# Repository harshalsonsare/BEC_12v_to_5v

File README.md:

# KiCad Hardware Design & Automation Workspace

A complete, production-verified hardware repository featuring a high-efficiency **12V-to-5V 3A Synchronous Buck Converter (BEC)**, engineered and verified using **KiCad 10** and the **KiCad MCP (Model Context Protocol) Server** in Google Antigravity.

---

## 3D Hardware & PCB Showcase

<p align="center">
  &nbsp;
  
</p>
<p align="center">
  <em>Figure 1: 3D Raytraced Model (Top) | Top Layer High-Current Routing & SilkS (Left) | Bottom Layer Shielded FB Trace & Solid GND (Right)</em>
</p>

<p align="center">
  <em>Figure 2: Verified Schematic (TI TPS54302, Protection Diode, Passives & Connectors)</em>
</p>

---

## 1. Project Overview & Specifications

### 12V-to-5V 3A Battery Eliminator Circuit (BEC)
Designed for robotics, UAV/FPV drones, RC models, and embedded computing (e.g. powering Raspberry Pi, flight controllers, and high-torque 5V servos from a 3S–4S LiPo battery or 12V DC rail).

| Parameter | Specification | Notes / Rationale |
| :--- | :--- | :--- |
| **Input Voltage ($V_{IN}$)** | **12 V nominal** (4.5 V – 18.0 V operational) | Compatible with 3S (11.1 V–12.6 V) and 4S (14.8 V–16.8 V) LiPo packs |
| **Input Transient Protection** | **SM6T18A TVS Diode** (600 W, $V_{RM} = 15.3\text{ V}$, $V_C = 25.2\text{ V}$) | Clamps voltage spikes safely below IC 30 V absolute max |
| **Output Voltage ($V_{OUT}$)** | **5.00 V DC** | Set via precision 0.5% divider ($R_1 = 93.1\text{ k}\Omega$, $R_2 = 12.6\text{ k}\Omega$) |
| **Output Current ($I_{OUT}$)** | **3.0 A continuous** | Thermally sustained on 2-layer 1 oz copper board |
| **Switching Frequency ($f_{SW}$)** | **400 kHz** fixed frequency | Optimized balance between size and switching efficiency |
| **Regulator IC** | **TI TPS54302DDCR** (SOT-23-6) | Synchronous buck converter with integrated 85 mΩ / 40 mΩ MOSFETs |
| **Power Inductor** | **Bourns SRP7028A-100M** (10 µH, shielded) | $I_{sat} = 6.0\text{ A}$, $I_{rms} = 3.5\text{ A}$, DCR = 75 mΩ |
| **Input Decoupling** | $22\ \mu\text{F}$ 35V X5R (1210) + $100\text{ nF}$ 50V X7R (0805) | High-voltage 1210 prevents severe ceramic DC bias capacitance drop |
| **Output Decoupling** | $2\times 22\ \mu\text{F}$ 25V X7R (1206) | Low ESR (< 10 mΩ), voltage ripple < 20 mV pk-pk at 3A load |
| **Phase Margin Boost** | $75\text{ pF}$ C0G feedforward cap ($C_8$) across $R_1$ | Stabilizes loop phase margin (>60°) with ceramic output capacitors |
| **UVLO Protection** | Precision divider: $R_3 = 511\text{ k}\Omega$, $R_4 = 105\text{ k}\Omega$ | Starts at ~6.9 V, stops at ~5.7 V; protects EN pin (7 V abs max) |
| **Input Connector ($J_1$)** | **AMASS XT30PW-M** (Horizontal / Right-Angle PCB) | High-reliability DC connector rated up to 30 A |
| **Output Connector ($J_2$)** | **3-Pin 2.54 mm Vertical Pin Header** | Standard RC servo pinout (Pin 1: NC/Signal, Pin 2: +5V, Pin 3: GND) |
| **PCB Dimensions** | **25.0 mm × 18.0 mm** | Centered on standard A4 sheet ($X = 148.5\text{ mm}, Y = 105.0\text{ mm}$) |
| **Layer Stackup** | **2-Layer FR-4**, 1.6 mm thickness, 1 oz Cu | Dual solid ground planes with thermal stitching array |
| **Design Status** | **100% Routed & Verified** | **0 DRC violations, 0 unconnected items, 0 ERC errors** |

---

## 2. Repository Structure

```text
KiCad/
├── .agents/
│   └── rules/
│       └── kicad-pcb.md           # Persistent agent engineering rules (always_on)
├── docs/
│   ├── images/                    # Visual renderings & documentation figures
│   │   ├── pcb_3d_isometric.png   # 3D raytraced PCB model
│   │   ├── pcb_top.png            # Top layer routing & silkscreen
│   │   ├── pcb_bottom.png         # Bottom layer shielded FB & ground plane
│   │   └── schematic.png          # Capture schematic overview
│   └── lessons-learned.md         # Persistent engineering memory, quirks & solutions
├── bec_12v_to_5v/                 # Core 12V-to-5V BEC KiCad project
│   ├── bec_12v_to_5v.kicad_pro    # Project settings & net classes
│   ├── bec_12v_to_5v.kicad_sch    # Schematic capture
│   ├── bec_12v_to_5v.kicad_pcb    # 25x18mm 2-layer routed board
│   ├── bec_12v_to_5v.kicad_dru    # Design rules
│   └── exports/                   # Project-local mirror of manufacturing outputs
├── DemoPCB/                       # MCP server interactive testing & validation board
│   ├── DemoPCB.kicad_pro
│   ├── DemoPCB.kicad_sch
│   └── DemoPCB.kicad_pcb
├── exports/                       # Production manufacturing & assembly packages
│   ├── gerbers/                   # RS-274X copper, soldermask, paste, silkscreen, edge cuts
│   ├── drill/                     # Excellon PTH & NPTH drill files and drill report
│   ├── bom/                       # Full Bill of Materials (CSV)
│   ├── pos/                       # Pick-and-place centroid coordinates (CSV)
│   ├── 3d/                        # Standard 3D CAD model (STEP AP214/AP242)
│   └── svg/                       # High-resolution vector renderings (top & bottom)
├── bec_12v_to_5v-drc.rpt          # Latest clean DRC report (0 errors, 0 warnings)
├── bec_12v_to_5v-erc.rpt          # Latest clean ERC report (0 errors, 0 warnings)
├── GEMINI.md                      # Agent pre-flight instructions & engineering guidelines
├── .gitignore                     # KiCad-optimized ignore rules (locks, backups, cache)
└── README.md                      # Project documentation and setup guide
```

---

## 3. Prerequisites & KiCad MCP Setup Guide

This project can be inspected and edited directly using the KiCad GUI or autonomously through the **KiCAD-MCP-Server**.

### Software Requirements
- **KiCad 10.0+** (`kicad`, `kicad-cli`, and `pcbnew` Python module)
- **Node.js 18+**
- **Python 3.10+** (with system `pcbnew` accessible)

### Configuring KiCAD-MCP-Server in Antigravity
The MCP server bridges Antigravity to KiCad's C++ routing and layout engine through `pcbnew` Python bindings.

Add the server to your `mcp_config.json` (typically located in `~/.gemini/config/mcp_config.json` or project root):

```json
{
  "mcpServers": {
    "kicad": {
      "command": "node",
      "args": [
        "/path/to/KiCAD-MCP-Server/dist/index.js"
      ],
      "env": {
        "KICAD_PYTHON": "/path/to/KiCAD-MCP-Server/venv/bin/python",
        "PYTHONPATH": "/usr/lib/kicad/lib/python3/dist-packages"
      }
    }
  }
}
```

> [!TIP]
> Ensure `PYTHONPATH` points to your system's KiCad Python dist-packages directory where `pcbnew.py` resides. On Ubuntu/Debian, this is `/usr/lib/kicad/lib/python3/dist-packages`.

---

## 4. Design & Verification Workflow

The design strictly adheres to a multi-gate verification pipeline:

```text
[ Schematic Capture ] ──> [ kicad-cli sch erc ] ──( 0 Errors )──> [ Netlist / PCB Sync ]
                                                                        │
[ DRC: 0 Violations ] <── [ Copper Pours & Vias ] <── [ Placement & Route ]
        │
        └───> [ Fabrication Exports (Gerber, Drill, POS, BOM, 3D STEP) ]
```

### Verification & Manufacturing Commands (`kicad-cli`)

#### 1. Electrical Rules Check (ERC)
Run ERC on the schematic to verify all pins are driven and connected:
```bash
kicad-cli sch erc --severity-all bec_12v_to_5v/bec_12v_to_5v.kicad_sch
```

#### 2. Design Rules Check (DRC)
Run DRC on the board with automatic polygon zone refill:
```bash
kicad-cli pcb drc --severity-all --refill-zones -o bec_12v_to_5v-drc.rpt bec_12v_to_5v/bec_12v_to_5v.kicad_pcb
```

#### 3. Export Manufacturing Gerbers
```bash
kicad-cli pcb export gerbers -o exports/gerbers/ --use-drill-file-origin bec_12v_to_5v/bec_12v_to_5v.kicad_pcb
```

#### 4. Export NC Drill Files
```bash
kicad-cli pcb export drill -o exports/drill/ --format excellon --generate-map --map-format gerber bec_12v_to_5v/bec_12v_to_5v.kicad_pcb
```

#### 5. Export Bill of Materials (BOM)
```bash
kicad-cli sch export bom -o exports/bom/bec_12v_to_5v_bom.csv bec_12v_to_5v/bec_12v_to_5v.kicad_sch
```

#### 6. Export Pick-and-Place Centroid (POS)
```bash
kicad-cli pcb export pos -o exports/pos/bec_12v_to_5v_pos.csv --format csv --units mm bec_12v_to_5v/bec_12v_to_5v.kicad_pcb
```

#### 7. Export 3D STEP Solid Model
```bash
kicad-cli pcb export step -o exports/3d/bec_12v_to_5v.step bec_12v_to_5v/bec_12v_to_5v.kicad_pcb
```

#### 8. Export Vector SVGs
```bash
kicad-cli pcb export svg -o exports/svg/bec_12v_to_5v_top.svg --page-size-mode 2 --layers F.Cu,F.SilkS,F.Mask,Edge.Cuts bec_12v_to_5v/bec_12v_to_5v.kicad_pcb
kicad-cli pcb export svg -o exports/svg/bec_12v_to_5v_bottom.svg --page-size-mode 2 --layers B.Cu,B.SilkS,B.Mask,Edge.Cuts bec_12v_to_5v/bec_12v_to_5v.kicad_pcb
```

---

## 5. Engineering Architecture & Layout Highlights

1. **Hot-Loop Priority**: Input capacitor $C_2$ (100 nF ceramic) connects directly to $U_1.3$ (`VIN`) and $U_1.1$ (`PGND`) on the top layer (`F.Cu`) without passing through vias first. Loop distance is < 3 mm to suppress high-frequency switching EMI.
2. **Short Switching Node**: The $SW$ track between IC pin 2, inductor $L_1$, and bootstrap capacitor $C_3$ is routed with 0.8 mm width and kept under 6 mm in length.
3. **Isolated Feedback Path**: The $FB$ trace is remote-sensed at output header $J_2$, drops to the bottom layer (`B.Cu`), and runs completely shielded underneath the continuous ground plane with >3 mm clearance from inductor $L_1$.
4. **Thermal Stitching**: Dedicated arrays of 0.6 mm vias tie top and bottom ground planes together around the power IC, TVS diode, and decoupling return paths.

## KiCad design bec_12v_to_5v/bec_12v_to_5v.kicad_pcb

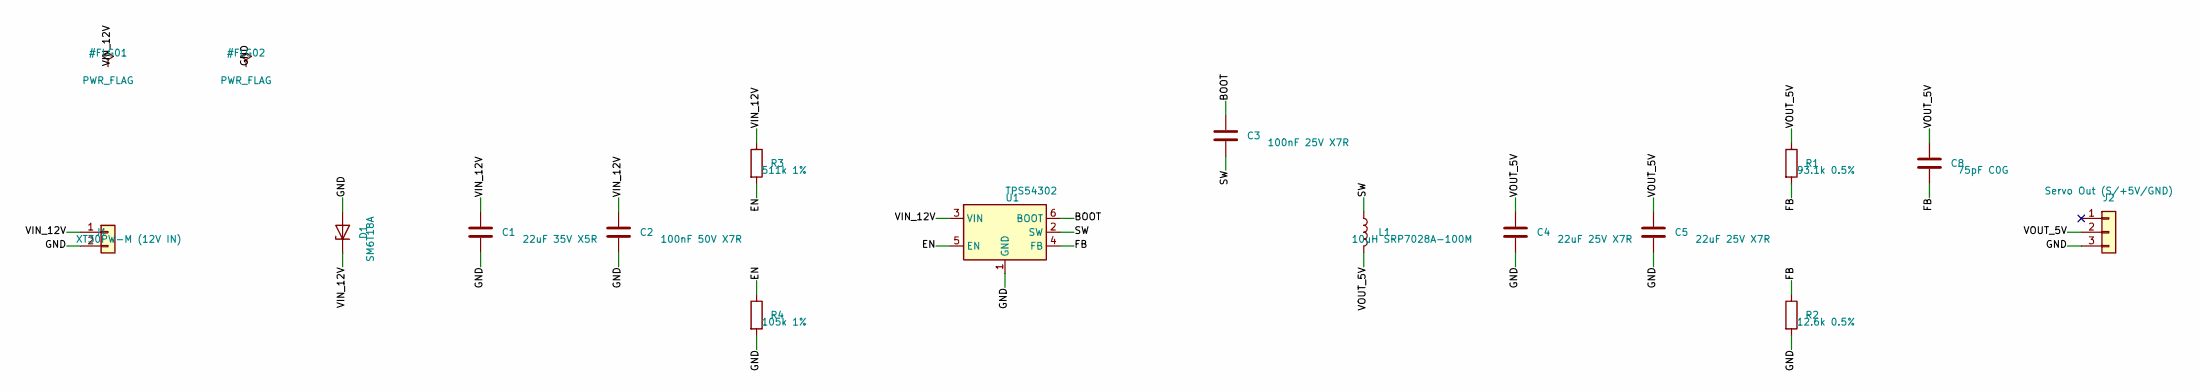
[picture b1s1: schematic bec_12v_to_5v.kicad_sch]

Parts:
C1: 22uF 35V X5R; C_1210_3225Metric
C2: 100nF 50V X7R; C_0805_2012Metric
C3: 100nF 25V X7R; C_0805_2012Metric
C4, C5: 22uF 25V X7R; C_1206_3216Metric
C8: 75pF C0G; C_0805_2012Metric
D1: SM6T18A; D_SMB
J1: XT30PW-M (12V IN); AMASS_XT30PW-M_1x02_P2.50mm_Horizontal
J2: Servo Out (S/+5V/GND); PinHeader_1x03_P2.54mm_Vertical
L1: 10uH SRP7028A-100M; L_Bourns_SRP7028A_7.3x6.6mm
R1: 93.1k 0.5%; R_0805_2012Metric
R2: 12.6k 0.5%; R_0805_2012Metric
R3: 511k 1%; R_0805_2012Metric
R4: 105k 1%; R_0805_2012Metric
U1: TPS54302; SOT-23-6

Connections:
/BOOT: C3.1, U1.6 (BOOT)
/EN: R3.2, R4.1, U1.5 (EN)
/FB: C8.2, R1.2, R2.1, U1.4 (FB)
/GND: C1.2, C2.2, C4.2, C5.2, D1.2 (A), J1.2, J2.3, R2.2, R4.2, U1.1 (GND)
/SW: C3.2, L1.1, U1.2 (SW)
/VIN_12V: C1.1, C2.1, D1.1 (K), J1.1, R3.1, U1.3 (VIN)
/VOUT_5V: C4.1, C5.1, C8.1, J2.2, L1.2, R1.1

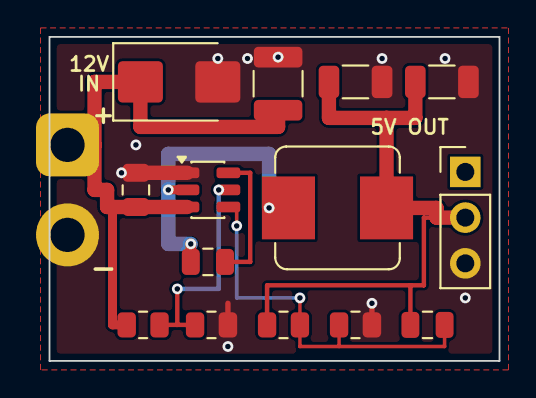
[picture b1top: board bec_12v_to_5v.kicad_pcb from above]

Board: 2 copper layers, 25.0 x 18.0 mm, 15 parts (0 on the bottom side), 7 nets.

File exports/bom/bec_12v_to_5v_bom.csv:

"Refs","Value","Footprint","Qty","DNP"
"C1","22uF 35V X5R","Capacitor_SMD:C_1210_3225Metric","1",""
"C2","100nF 50V X7R","Capacitor_SMD:C_0805_2012Metric","1",""
"C3","100nF 25V X7R","Capacitor_SMD:C_0805_2012Metric","1",""
"C4","22uF 25V X7R","Capacitor_SMD:C_1206_3216Metric","1",""
"C5","22uF 25V X7R","Capacitor_SMD:C_1206_3216Metric","1",""
"C8","75pF C0G","Capacitor_SMD:C_0805_2012Metric","1",""
"D1","SM6T18A","Diode_SMD:D_SMB","1",""
"J1","XT30PW-M (12V IN)","Connector_AMASS:AMASS_XT30PW-M_1x02_P2.50mm_Horizontal","1",""
"J2","Servo Out (S/+5V/GND)","Connector_PinHeader_2.54mm:PinHeader_1x03_P2.54mm_Vertical","1",""
"L1","10uH SRP7028A-100M","Inductor_SMD:L_Bourns_SRP7028A_7.3x6.6mm","1",""
"R1","93.1k 0.5%","Resistor_SMD:R_0805_2012Metric","1",""
"R2","12.6k 0.5%","Resistor_SMD:R_0805_2012Metric","1",""
"R3","511k 1%","Resistor_SMD:R_0805_2012Metric","1",""
"R4","105k 1%","Resistor_SMD:R_0805_2012Metric","1",""
"U1","TPS54302","Package_TO_SOT_SMD:SOT-23-6","1",""

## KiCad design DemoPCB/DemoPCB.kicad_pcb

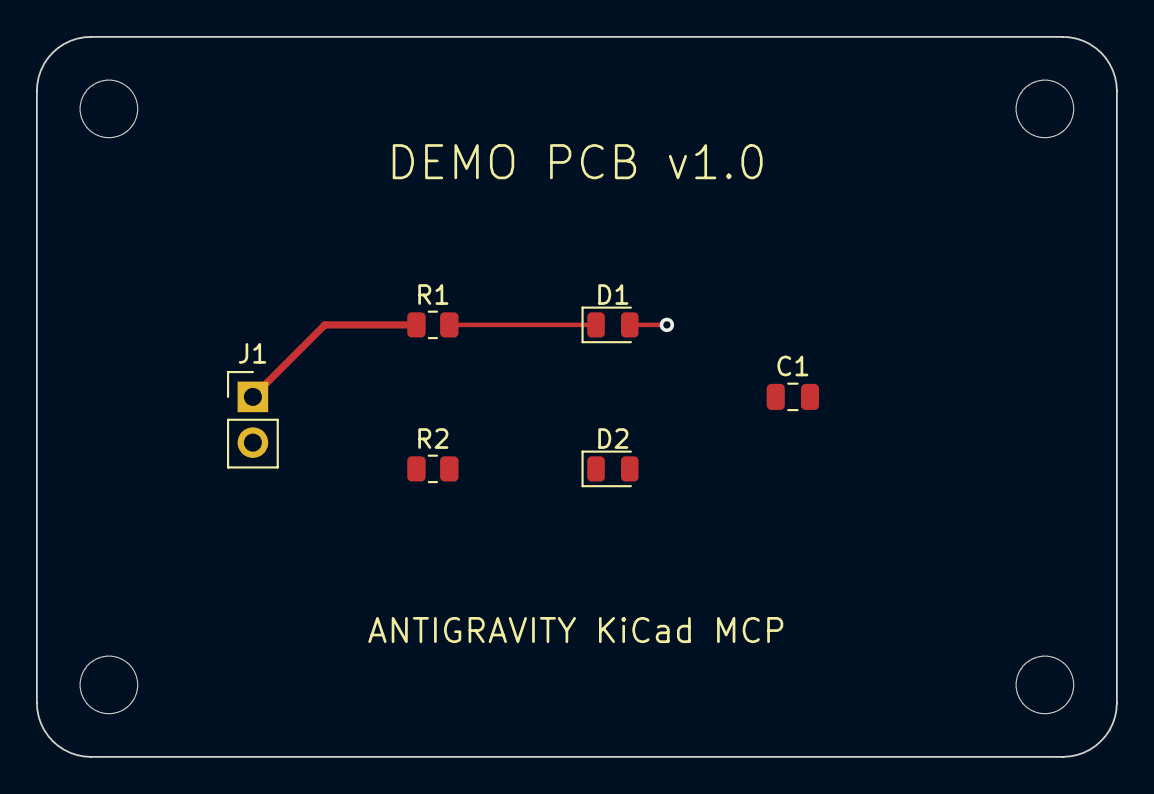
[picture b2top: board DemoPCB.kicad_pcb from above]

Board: 2 copper layers, 60.0 x 40.0 mm, 10 parts (0 on the bottom side), 3 nets.

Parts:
C1: 10uF; C_0805_2012Metric
D1: LED_GREEN; LED_0805_2012Metric
D2: LED_BLUE; LED_0805_2012Metric
J1: PWR_IN; PinHeader_1x02_P2.54mm_Vertical
MH1, MH2, MH3, MH4: MountingHole_3.2mm_M3
R1: 1k; R_0805_2012Metric
R2: 330R; R_0805_2012Metric

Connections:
GND: D1.2, J1.2
NET_LED1: D1.1, R1.2
VCC: J1.1, R1.1
